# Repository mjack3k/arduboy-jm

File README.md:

# Arduboy JM
My homebrew clone of arduboy - arduino-based handheld game console

For the original Arduboy please visit [their website](https://www.arduboy.com/)
<br/>
<br/>

## Description
This project differs a bit from the official arduboy. 
It follows the alternate **Pro Micro 5V alternate wiring**.
All buttons have pull-up resistors and debounce filter (resistor + capacitor).

Battery charging and 5V boost circuit is also a bit over-engineered - I stole that part from my other project idea that was meant for powering raspberry pi.
In theory it could deliver over 3A, if proper LiPo battery was used. 

It is a bit bigger - no longer credit-card sized, but I believe it makes it more comfortable to use. 

And since we're in 2023 already, I used USB-C connector instead of microUSB.
Also added ESD-protection IC on the USB port. 

This arduboy has the **FX-Mod** on board - a SPI-Flash chip to hold all the games.

<br/><br/>
## How to make one?
+ Install [KICAD](https://www.kicad.org/), open the project and generate gerber files (there are guides on how to do it depending on the manufacturer).

+ Order the PCB (I ordered mine at [JCLPCB](https://jlcpcb.com/), no issues so far).

+ Order the parts (all parts* are available at LCSC, but you can source your parts at different suppliers).

+ Solder everything together.

+ Flash the bootloader [*arduboy3k-bootloader-menu-promicro-sh1106.hex*](https://github.com/MrBlinky/cathy3k/tree/main/cathy3k)
<br/>You will need avr isp programmer for that, like [AVRISP MKII](https://www.microchip.com/en-us/development-tool/ATAVRISP2), [USBASP](https://www.fischl.de/usbasp/) or [Arduino as ISP](https://docs.arduino.cc/built-in-examples/arduino-isp/ArduinoISP) and [AVRDUDE](https://github.com/mariusgreuel/avrdude/releases) installed.
<br/>Flash the bootloader with following command (replace COM port and path to .hex file accordingly):
`avrdude -v -p m32u4 -c avrisp -B 22 -b 19200 -P COM4 -U flash:w:arduboy3k-bootloader-game-promicro-sh1106.hex:i`
+ Flash the flashcart 
<br/>This part is tricky, since it involves recompiling all games. On one hand, thanks to great people at arduboy.com, we are able to compile games for different hardware thanks to Homemade package.
<br/>On other hand, arduino IDE is a **BAD** IDE and it is tricky to automate the process (doing it by hand is annoying, since there are 300? 400? games available). 
    + Install [Arduino](https://www.arduino.cc/en/software) and [Homemade Package](https://github.com/MrBlinky/Arduboy-homemade-package)
    + Download [Python Utilities from MrBlinky](https://github.com/MrBlinky/Arduboy-Python-Utilities) (for building flashcard image)
    + Download game source (look for github repositories [here](http://www.bloggingadeadhorse.com/cart/Cart.html))
    + Set board settings like on the picture
    <br/>
    + Place the compiled .hex file in directory structure (check example from Python Utilities)
    + Build flashcart ([how](https://github.com/MrBlinky/Arduboy-Python-Utilities#flash-cart-builder))
    + Download [this project](https://github.com/MrBlinky/Arduboy-FX-mod-chip) to get GUI uploader - extract zip from `portable-activator`
    + Select your .bin file and click `Upload Flash image`

<br/>

## Future
In the future I intend to work more on the software side of thise project.
Mainly, I wish to automate the build process, so a script would gather all the games, compile them, place in flashcart directory, generate CSV file and provide a complete BIN for the FX-Mod without manual labor.

<br/>

### Display
I used cheaper SH1106 (SPI) display, but if you get ssd1306 then change your settings to fit (also get different bootloader file).

<br/>

### Battery charging circuit warning
Charging current is related to capacity of the battery. 
Please change the R28 resistor accordingly if you are using smaller LiPos, cause they might not like 500mA charging current. I wouldn't set it to higher current either, cause then it might not work when connected to PC (you will connect to your PC to flash the games).

<br/><br/><br/>
*all parts besides LiPo battery, piezo speaker and display
<br/>Best source for display is ebay, aliexpress or your local online shop for makers.
Speakers can be extracted from old hardware, otherwise similar like display.
LiPo batteries are best bought from local shops, cause they dont want to send them by air, and the prices might vary greatly depending on your location. 
<br/>
Also, you choose the battery you are okay with - differents shapes and sizes available. The project will work even with pretty small batteries, but nothing stops you from putting really big one if you want it.

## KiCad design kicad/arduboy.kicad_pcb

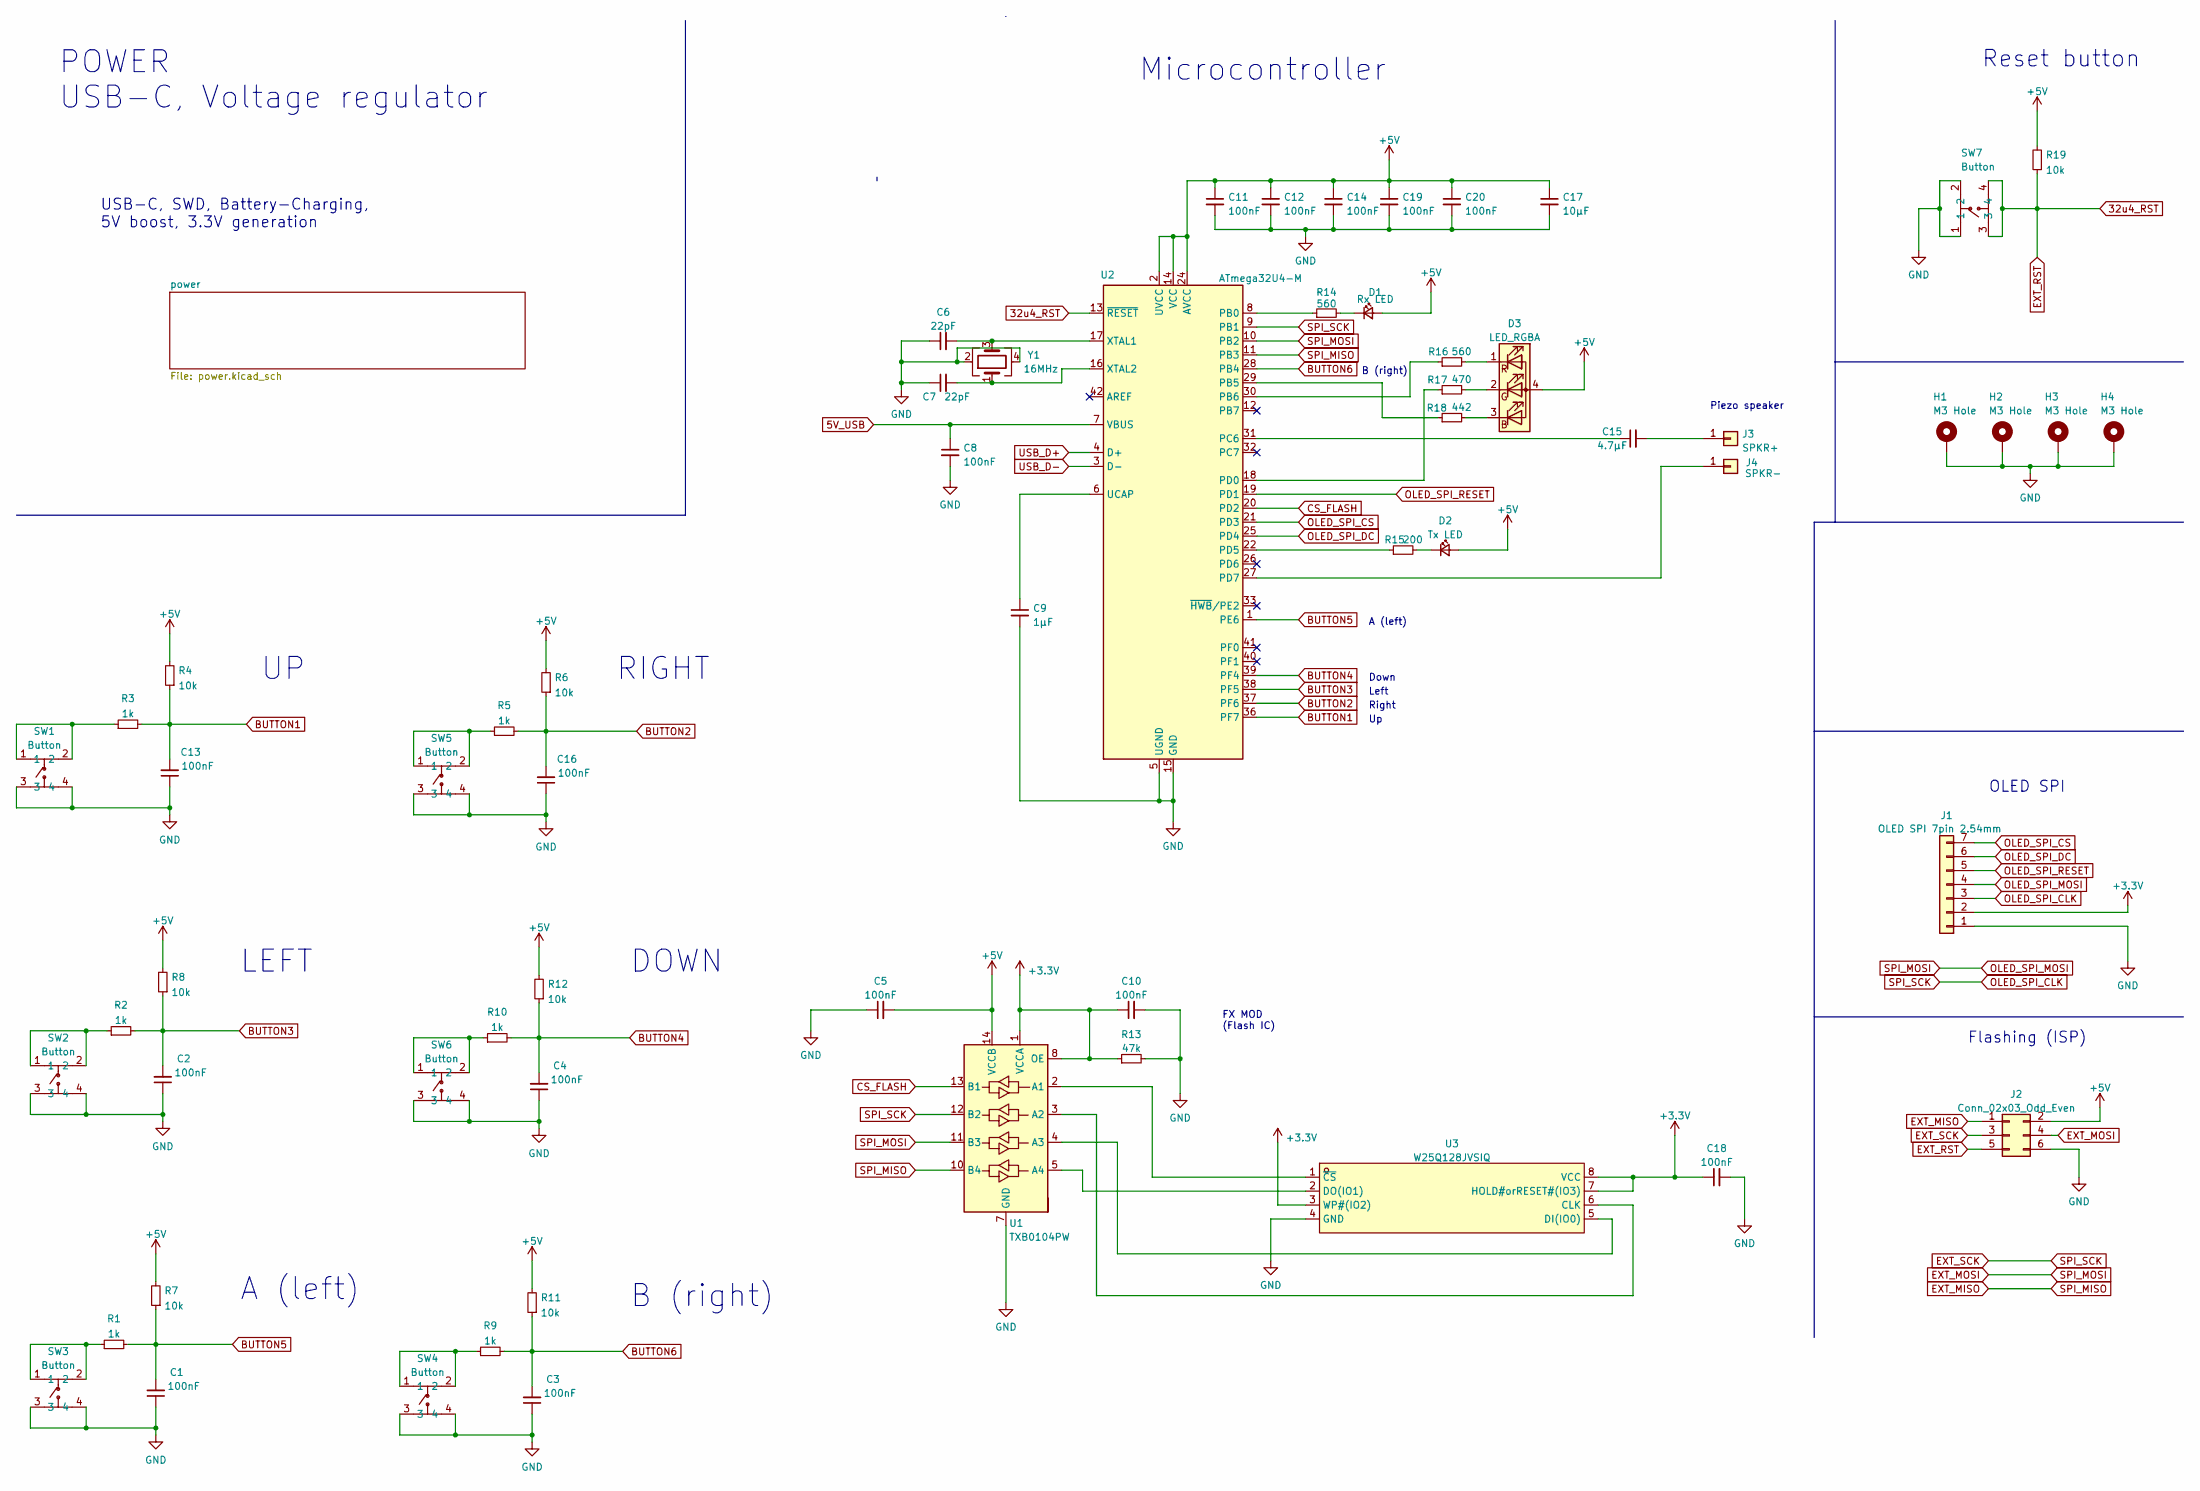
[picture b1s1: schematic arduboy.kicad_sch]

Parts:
C1, C2, C3, C4, C5, C8, C10, C11, C12, C13, C14, C16, C18, C19, C20: 100nF; C_0603_1608Metric_Pad1.08x0.95mm_HandSolder
C6, C7: 22pF; C_0603_1608Metric_Pad1.08x0.95mm_HandSolder
C9: 1µF; C_0603_1608Metric_Pad1.08x0.95mm_HandSolder
C15: 4.7µF; C_0603_1608Metric
C17: 10µF; C_0603_1608Metric_Pad1.08x0.95mm_HandSolder
D1: Rx LED; LED_0805_2012Metric_Pad1.15x1.40mm_HandSolder
D2: Tx LED; LED_0805_2012Metric_Pad1.15x1.40mm_HandSolder
D3: LED_RGBA; LED-ARRAY-SMD_4P-L2.1-W2.1-TL_NH-B2020RGBA
H1, H2, H3, H4: M3 Hole; MountingHole_3.2mm_M3_Pad_Via
J1: OLED SPI 7pin 2.54mm; OLED_7_Pin
J2: Conn_02x03_Odd_Even; PinSocket_2x03_P2.54mm_Vertical
J3: SPKR+; TestPoint_Pad_4.0x4.0mm
J4: SPKR-; TestPoint_Pad_4.0x4.0mm
R1, R2, R3, R5, R9, R10: 1k; R_0603_1608Metric_Pad0.98x0.95mm_HandSolder
R4, R6, R7, R8, R11, R12, R19: 10k; R_0603_1608Metric_Pad0.98x0.95mm_HandSolder
R13: 47k; R_0603_1608Metric_Pad0.98x0.95mm_HandSolder
R14, R16: 560; R_0603_1608Metric_Pad0.98x0.95mm_HandSolder
R15: 200; R_0603_1608Metric_Pad0.98x0.95mm_HandSolder
R17: 470; R_0603_1608Metric_Pad0.98x0.95mm_HandSolder
R18: 442; R_0603_1608Metric_Pad0.98x0.95mm_HandSolder
SW1, SW2, SW3, SW4, SW5, SW6, SW7: Button; SW-SMD_4P-L5.2-W5.2-P3.70-LS6.4; LCSC Part C2888878
U1: TXB0104PW; TSSOP-14_4.4x5mm_P0.65mm
U2: ATmega32U4-M; QFN-44-1EP_7x7mm_P0.5mm_EP5.2x5.2mm
U3: W25Q128JVSIQ; SOIC-8_L5.3-W5.3-P1.27-LS8.0-BL; LCSC Part C113767
Y1: 16MHz; CRYSTAL-SMD_4P-L3.2-W2.5-BL

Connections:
5V_USB: C8.1, U2.7 (VBUS); also elsewhere on the board
32u4_RST: J2.5, R19.1, SW7.3, SW7.4, U2.13 (~RESET)
+3.3V: C10.1, C18.1, J1.2, R13.1, U1.1 (VCCA), U1.8 (OE), U3.3 (WP#(IO2)), U3.7 (HOLD#orRESET#(IO3)), U3.8 (VCC); also elsewhere on the board
+5V: C5.2, C11.1, C12.1, C14.1, C17.1, C19.1, C20.1, D1.2 (A), D2.2 (A), D3.4 (A), J2.2, R4.2, R6.2, R7.2, R8.2, R11.2, R12.2, R19.2, U1.14 (VCCB), U2.2 (UVCC), U2.14 (VCC), U2.24 (AVCC), U2.34 (VCC), U2.44 (AVCC); also elsewhere on the board
BUTTON1: C13.2, R3.2, R4.1, U2.36 (PF7)
BUTTON2: C16.2, R5.2, R6.1, U2.37 (PF6)
BUTTON3: C2.2, R2.2, R8.1, U2.38 (PF5)
BUTTON4: C4.2, R10.2, R12.1, U2.39 (PF4)
BUTTON5: C1.2, R1.2, R7.1, U2.1 (PE6)
BUTTON6: C3.2, R9.2, R11.1, U2.28 (PB4)
CS_FLASH: U1.13 (B1), U2.20 (PD2)
EXT_MISO: J2.1, U1.10 (B4), U2.11 (PB3)
EXT_MOSI: J1.4, J2.4, U1.11 (B3), U2.10 (PB2)
EXT_SCK: J1.3, J2.3, U1.12 (B2), U2.9 (PB1)
GND: C1.1, C2.1, C3.1, C4.1, C5.1, C6.1, C7.1, C8.2, C9.2, C10.2, C11.2, C12.2, C13.1, C14.2, C16.1, C17.2, C18.2, C19.2, C20.2, H1.1, H2.1, H3.1, H4.1, J1.1, J2.6, R13.2, SW1.3, SW1.4, SW2.3, SW2.4, SW3.3, SW3.4, SW4.3, SW4.4, SW5.3, SW5.4, SW6.3, SW6.4, SW7.1, SW7.2, U1.7 (GND), U2.5 (UGND), U2.15 (GND), U2.23 (GND), U2.35 (GND), U2.43 (GND), U2.45 (GND), U3.4 (GND), Y1.2, Y1.4; also elsewhere on the board
unnamed: C6.2, U2.17 (XTAL1), Y1.3
unnamed: C7.2, U2.16 (XTAL2), Y1.1
unnamed: C9.1, U2.6 (UCAP)
unnamed: C15.1, U2.31 (PC6)
unnamed: C15.2, J3.1
unnamed: D1.1 (K), R14.2
unnamed: D2.1 (K), R15.2
unnamed: D3.1 (RK), R16.2
unnamed: D3.2 (GK), R17.2
unnamed: D3.3 (BK), R18.2
unnamed: R1.1, SW3.1, SW3.2
unnamed: R2.1, SW2.1, SW2.2
unnamed: R3.1, SW1.1, SW1.2
unnamed: R5.1, SW5.1, SW5.2
unnamed: R9.1, SW4.1, SW4.2
unnamed: R10.1, SW6.1, SW6.2
unnamed: R14.1, U2.8 (PB0)
unnamed: R15.1, U2.22 (PD5)
unnamed: R16.1, U2.30 (PB6)
unnamed: R17.1, U2.18 (PD0)
unnamed: R18.1, U2.29 (PB5)
unnamed: U1.2 (A1), U3.1 (~CS)
unnamed: U1.3 (A2), U3.6 (CLK)
unnamed: U1.4 (A3), U3.5 (DI(IO0))
unnamed: U1.5 (A4), U3.2 (DO(IO1))
unnamed: J4.1, U2.27 (PD7)
OLED_SPI_CS: J1.7, U2.21 (PD3)
OLED_SPI_DC: J1.6, U2.25 (PD4)
OLED_SPI_RESET: J1.5, U2.19 (PD1)
USB_D+: U2.4 (D+); also elsewhere on the board
USB_D-: U2.3 (D-); also elsewhere on the board

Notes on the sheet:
Reset button
Right
Piezo speaker
Left
Microcontroller
LEFT
B (right)
POWER USB-C, Voltage regulator
Down
A (left)
FX MOD (Flash IC)
RIGHT
USB-C, SWD, Battery-Charging, 5V boost, 3.3V generation
Flashing (ISP)
OLED SPI
DOWN

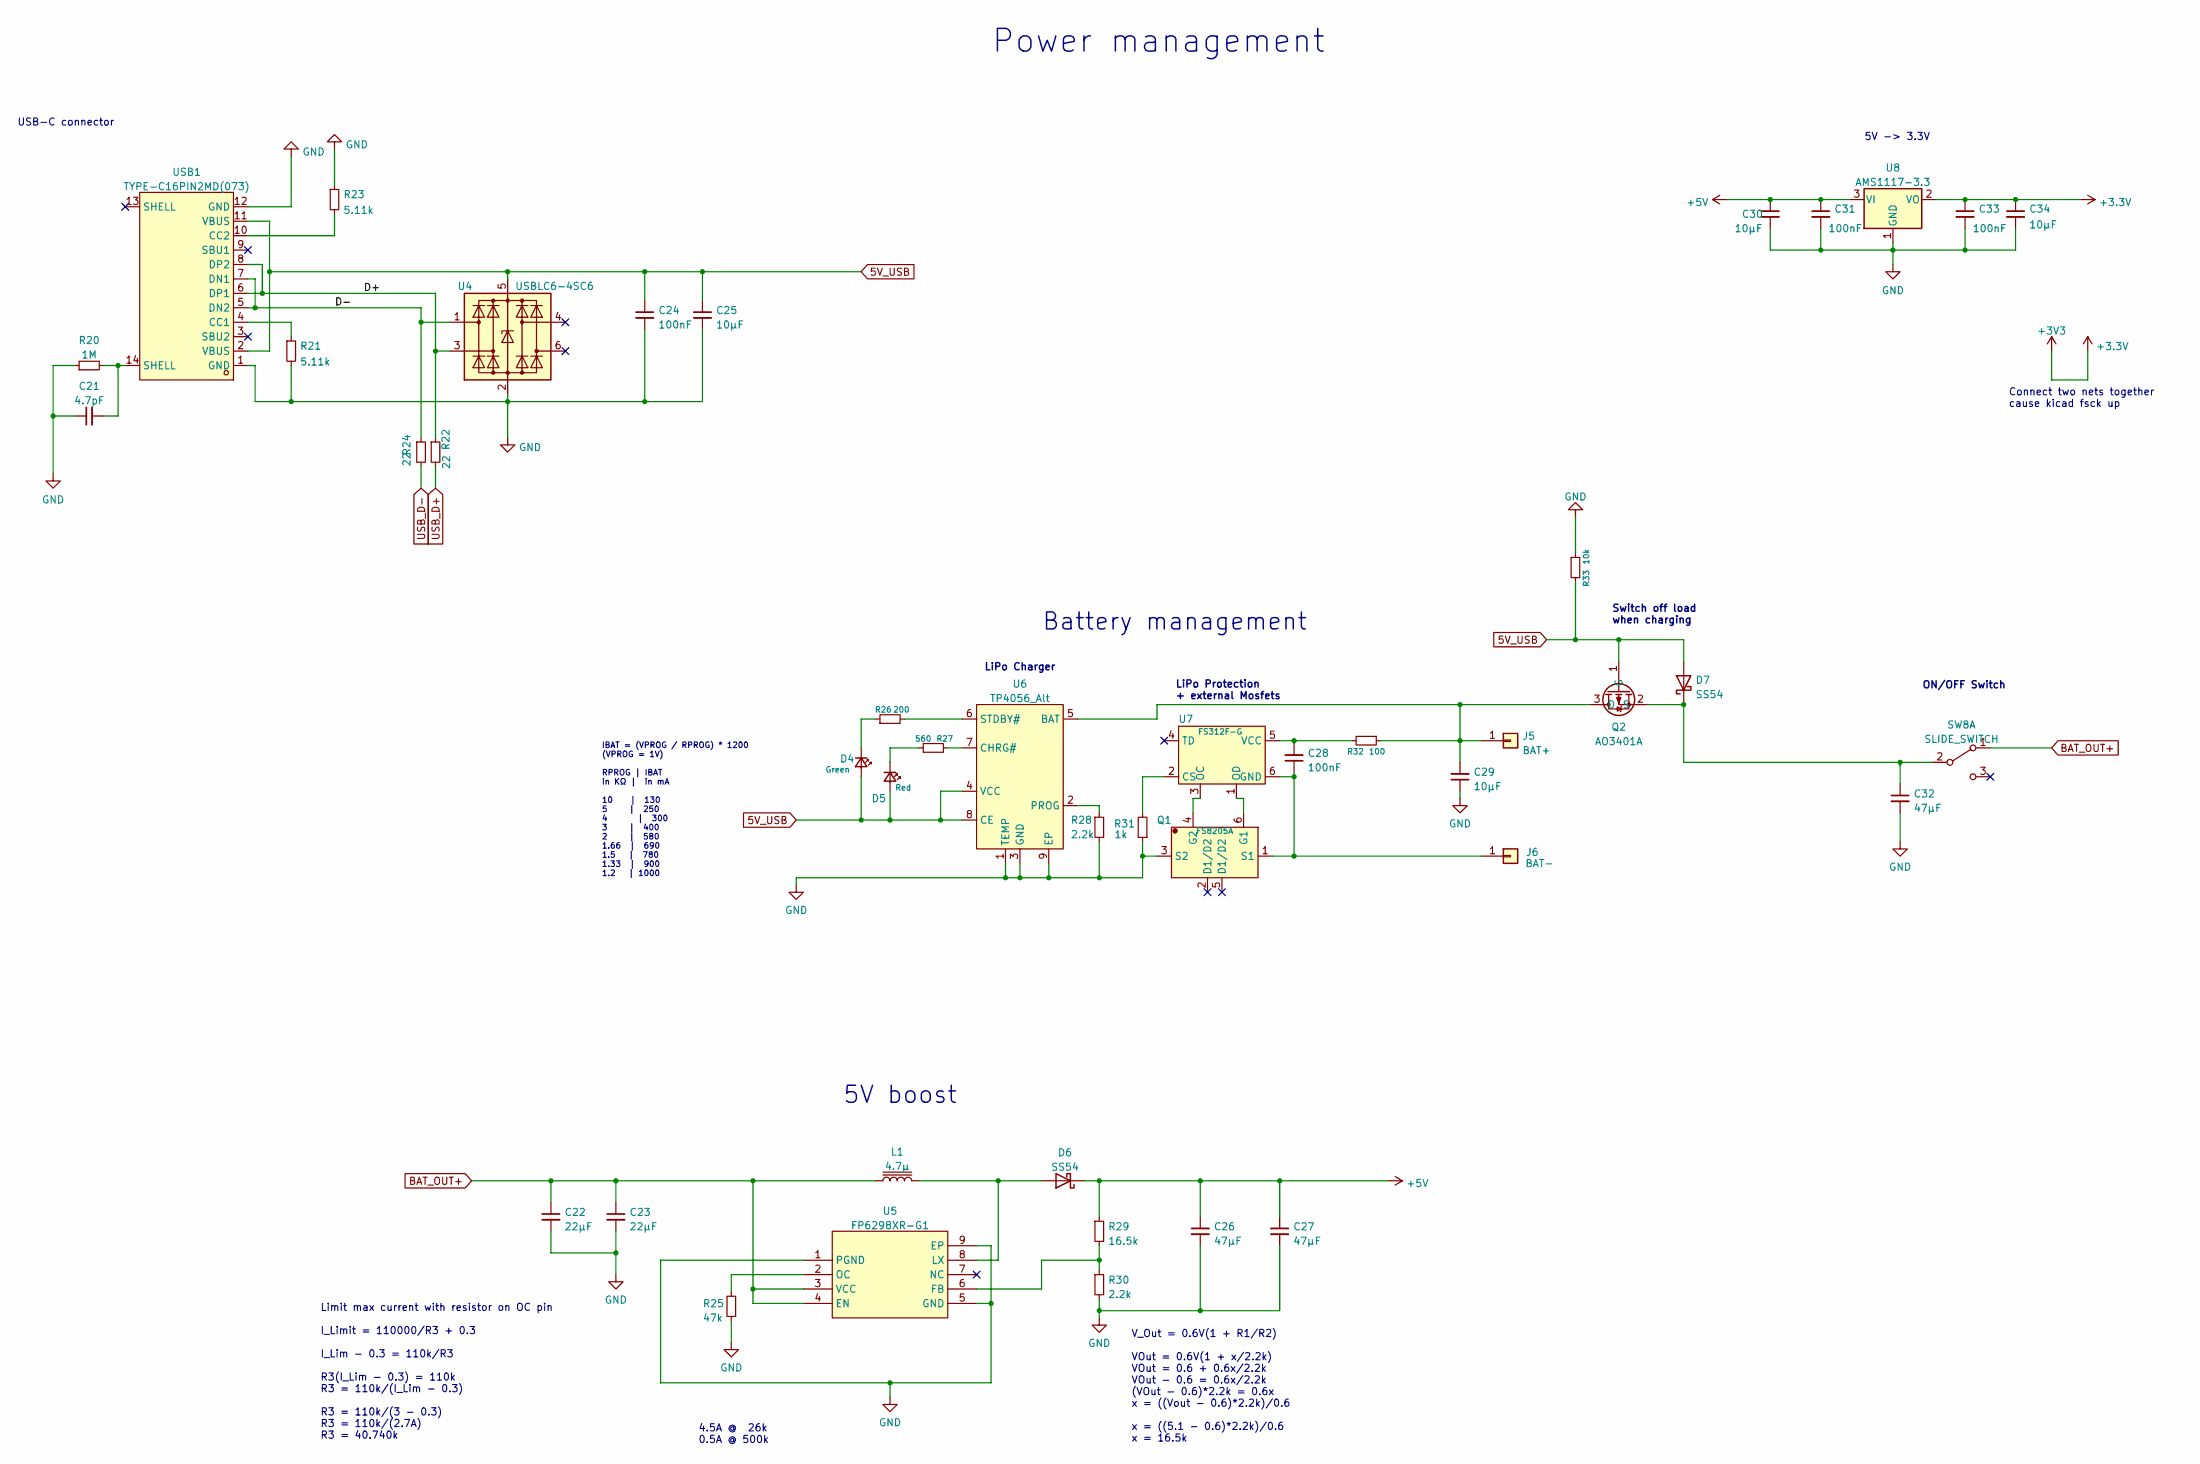
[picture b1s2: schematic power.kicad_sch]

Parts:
C21: 4.7pF; C_0603_1608Metric_Pad1.08x0.95mm_HandSolder
C22, C23: 22µF; C_0603_1608Metric_Pad1.08x0.95mm_HandSolder
C24, C28, C31, C33: 100nF; C_0603_1608Metric_Pad1.08x0.95mm_HandSolder
C25, C29, C30, C34: 10µF; C_0603_1608Metric_Pad1.08x0.95mm_HandSolder
C26, C27, C32: 47µF; C_1210_3225Metric_Pad1.33x2.70mm_HandSolder
D4: Green; LED_0805_2012Metric_Pad1.15x1.40mm_HandSolder
D5: Red; LED_0805_2012Metric_Pad1.15x1.40mm_HandSolder
D6, D7: SS54; SMA_L4.4-W2.8-LS5.4-R-RD
J5: BAT+; TestPoint_Pad_4.0x4.0mm
J6: BAT-; TestPoint_Pad_4.0x4.0mm
L1: 4.7µ; IND-SMD_L7.3-W6.6
Q1: FS8205A; SOT-23-6_L2.9-W1.6-P0.95-LS2.8-BR
Q2: AO3401A; SOT-23_L2.9-W1.3-P1.90-LS2.4-BR
R20: 1M; R_0603_1608Metric_Pad0.98x0.95mm_HandSolder
R21, R23: 5.11k; R_0603_1608Metric_Pad0.98x0.95mm_HandSolder
R22, R24: 22; R_0603_1608Metric_Pad0.98x0.95mm_HandSolder
R25: 47k; R_0603_1608Metric_Pad0.98x0.95mm_HandSolder
R26: 200; R_0603_1608Metric_Pad0.98x0.95mm_HandSolder
R27: 560; R_0603_1608Metric_Pad0.98x0.95mm_HandSolder
R28, R30: 2.2k; R_0603_1608Metric_Pad0.98x0.95mm_HandSolder
R29: 16.5k; R_0603_1608Metric_Pad0.98x0.95mm_HandSolder
R31: 1k; R_0603_1608Metric_Pad0.98x0.95mm_HandSolder
R32: 100; R_0603_1608Metric_Pad0.98x0.95mm_HandSolder
R33: 10k; R_0603_1608Metric_Pad0.98x0.95mm_HandSolder
SW8: SLIDE_SWITCH; SW-TH_SK-12D07-X-X
U4: USBLC6-4SC6; SOT-23-6
U5: FP6298XR-G1; SOP-8_L4.9-W3.9-P1.27-LS6.0-BL-EP; LCSC Part C88319
U6: TP4056_Alt; ESOP-8_L4.9-W3.9-P1.27-LS6.0-BL-EP
U7: FS312F-G; SOT-23-6_L2.9-W1.6-P0.95-LS2.8-BR
U8: AMS1117-3.3; SOT-223_L6.5-W3.5-P2.30-LS7.0-BR
USB1: TYPE-C16PIN2MD(073); USB-C-SMD_TYPE-C-6PIN-2MD-073; LCSC Part C2765186

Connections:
5V_USB: C24.1, C25.1, D4.2 (A), D5.2 (A), D7.2 (A), Q2.1 (G), R33.2, U4.5 (VBUS), U6.4 (VCC), U6.8 (CE), USB1.2 (VBUS), USB1.11 (VBUS); also elsewhere on the board
+3.3V: C33.1, C34.1, U8.2 (VO); also elsewhere on the board
+5V: C26.1, C27.1, C30.1, C31.1, D6.1 (K), R29.1, U8.3 (VI); also elsewhere on the board
/power/D+: R22.1, U4.3 (I/O2), USB1.6 (DP1), USB1.8 (DP2)
/power/D-: R24.1, U4.1 (I/O1), USB1.5 (DN2), USB1.7 (DN1)
BAT_OUT+: C22.1, C23.1, L1.1, SW8.1 (A), U5.3 (VCC), U5.4 (EN)
GND: C21.1, C22.2, C23.2, C24.2, C25.2, C26.2, C27.2, C29.1, C30.2, C31.2, C32.2, C33.2, C34.2, Q1.3 (S2), R20.1, R21.2, R23.1, R25.1, R28.2, R30.2, R31.1, R33.1, U4.2 (GND), U5.1 (PGND), U5.5 (GND), U5.9 (EP), U6.1 (TEMP), U6.3 (GND), U6.9 (EP), U8.1 (GND), USB1.1 (GND), USB1.12 (GND); also elsewhere on the board
unnamed: C21.2, R20.2, USB1.14 (SHELL)
unnamed: C28.1, J6.1, Q1.1 (S1), U7.6 (GND)
unnamed: C28.2, R32.2, U7.5 (VCC)
unnamed: C29.2, J5.1, Q2.3 (D), R32.1, U6.5 (BAT)
unnamed: C32.1, D7.1 (K), Q2.2 (S), SW8.2 (B)
unnamed: D4.1 (K), R26.1
unnamed: D5.1 (K), R27.1
unnamed: D6.2 (A), L1.2, U5.8 (LX)
unnamed: Q1.4 (G2), U7.3 (OC)
unnamed: Q1.6 (G1), U7.1 (OD)
unnamed: R21.1, USB1.4 (CC1)
unnamed: R23.2, USB1.10 (CC2)
unnamed: R25.2, U5.2 (OC)
unnamed: R26.2, U6.6 (STDBY#)
unnamed: R27.2, U6.7 (CHRG#)
unnamed: R28.1, U6.2 (PROG)
unnamed: R29.2, R30.1, U5.6 (FB)
unnamed: R31.2, U7.2 (CS)
USB_D+: R22.2; also elsewhere on the board
USB_D-: R24.2; also elsewhere on the board

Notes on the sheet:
ON/OFF Switch
Battery management
Switch off load when charging
V_Out = 0.6V(1 + R1/R2) VOut = 0.6V(1 + x/2.2k) VOut = 0.6 + 0.6x/2.2k VOut - 0.6 = 0.6x/2.2k (VOut - 0.6)*2.2k = 0.6x x = ((Vout - 0.6)*2.2k)/0.6 x = ((5.1 - 0.6)*2.2k)/0.6 x = 16.5k
Connect two nets together cause kicad fsck up
5V boost
USB-C connector
Power management
5V -> 3.3V
LiPo Protection + external Mosfets
LiPo Charger
4.5A @ 26k 0.5A @ 500k
Limit max current with resistor on OC pin I_Limit = 110000/R3 + 0.3 I_Lim - 0.3 = 110k/R3 R3(I_Lim - 0.3) = 110k R3 = 110k/(I_Lim - 0.3) R3 = 110k/(3 - 0.3) R3 = 110k/(2.7A) R3 = 40.740k
IBAT = (VPROG / RPROG) * 1200 (VPROG = 1V) RPROG | IBAT in KΩ | in mA 10 | 130 5 | 250 4 | 300 3 | 400 2 | 580 1.66 | 690 1.5 | 780 1.33 | 900 1.2 | 1000

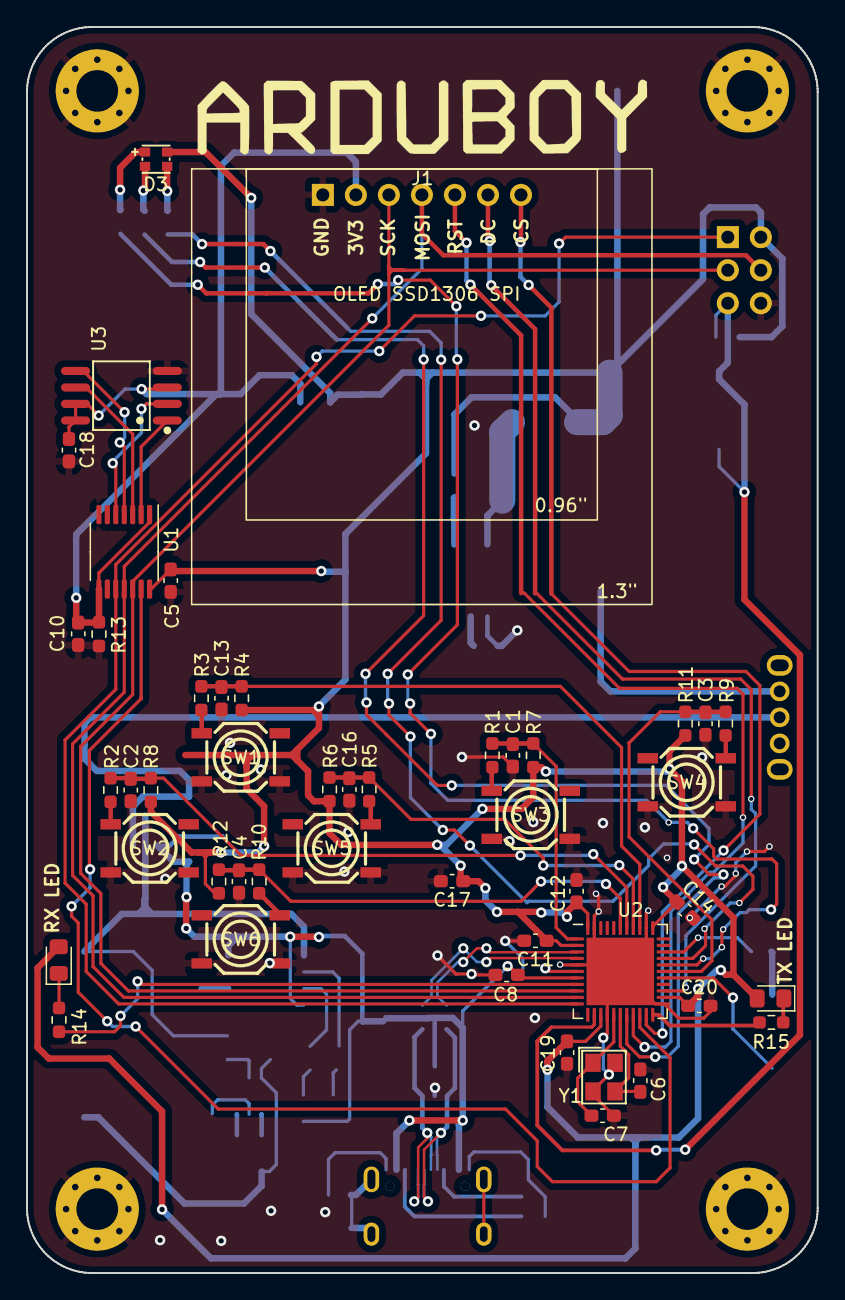
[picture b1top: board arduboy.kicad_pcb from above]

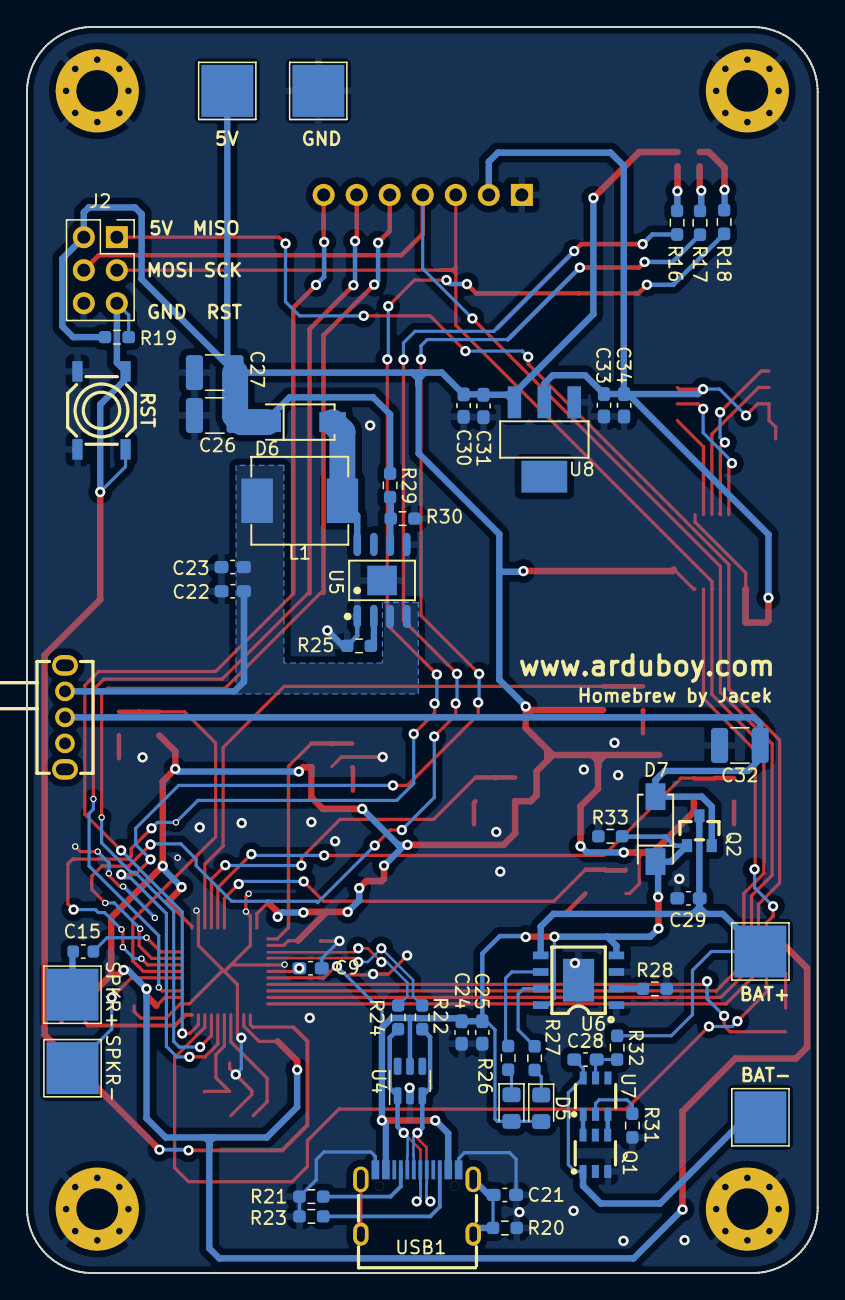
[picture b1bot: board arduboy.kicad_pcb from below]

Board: 2 copper layers, 60.8 x 95.8 mm, 105 parts (54 on the bottom side), 67 nets.

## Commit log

2023-04-16 Add readme and .gitignore
2023-04-16 Fix README
